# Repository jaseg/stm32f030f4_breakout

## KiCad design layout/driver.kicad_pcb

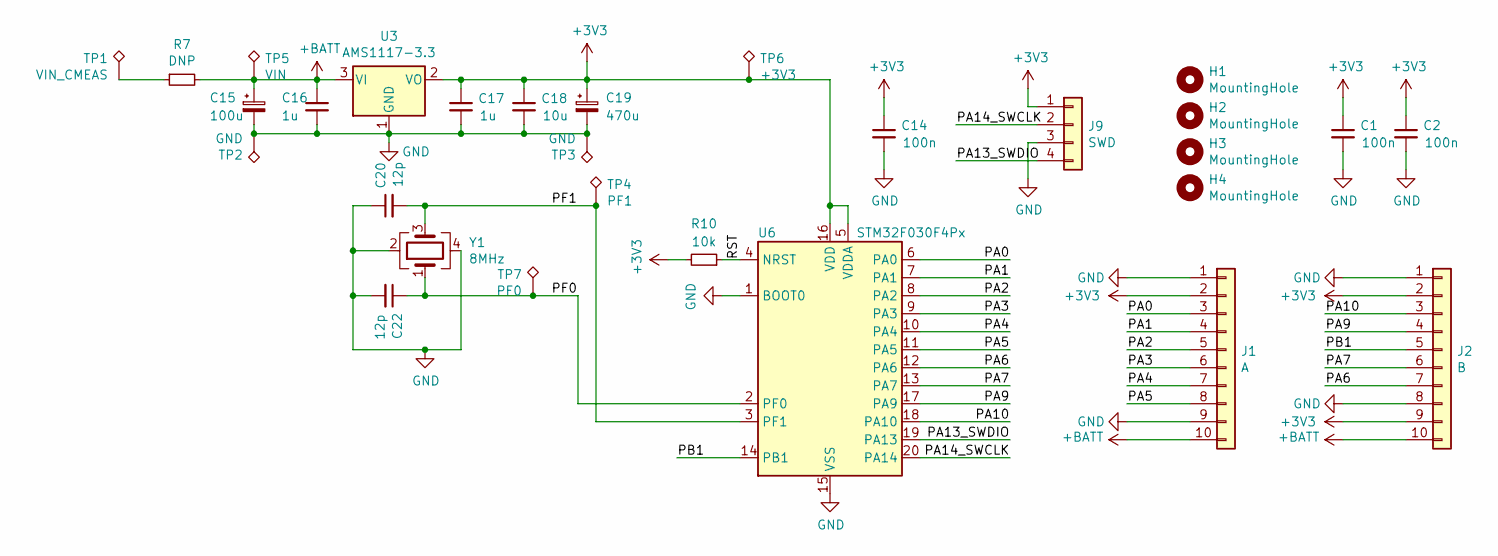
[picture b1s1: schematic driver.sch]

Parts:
C1, C2, C14: 100n; C_0603_1608Metric_Pad1.05x0.95mm_HandSolder
C15: 100u; CP_Radial_D6.3mm_P2.50mm
C16, C17: 1u; C_0603_1608Metric_Pad1.05x0.95mm_HandSolder
C18: 10u; C_0603_1608Metric_Pad1.05x0.95mm_HandSolder
C19: 470u; CP_Radial_D6.3mm_P2.50mm
C20, C22: 12p; C_0603_1608Metric_Pad1.05x0.95mm_HandSolder
H1, H2, H3, H4: MountingHole; MountingHole_3.2mm_M3
J1: A; PinHeader_1x10_P2.54mm_Vertical
J2: B; PinHeader_1x10_P2.54mm_Vertical
J9: SWD; PinHeader_1x04_P2.54mm_Vertical
R7: DNP; R_0603_1608Metric_Pad1.05x0.95mm_HandSolder
R10: 10k; R_0603_1608Metric_Pad1.05x0.95mm_HandSolder
TP1: VIN_CMEAS; TestPoint_Pad_D1.5mm
TP2: GND; TestPoint_Pad_D2.5mm
TP3: GND; TestPoint_Pad_D1.5mm
TP4: PF1; TestPoint_Pad_D1.5mm
TP5: VIN; TestPoint_Pad_D2.5mm
TP6: +3V3; TestPoint_Pad_D1.5mm
TP7: PF0; TestPoint_Pad_D1.5mm
U3: AMS1117-3.3; SOT-223-3_TabPin2
U6: STM32F030F4Px; TSSOP-20_4.4x6.5mm_P0.65mm
Y1: 8MHz; Crystal_SMD_3225-4Pin_3.2x2.5mm_HandSoldering

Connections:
+3V3: C1.1, C2.1, C14.1, C17.1, C18.1, C19.1, J1.2, J2.2, J2.9, J9.1, R10.2, TP6.1, U3.2 (VO), U6.5 (VDDA), U6.16 (VDD); also elsewhere on the board
+BATT: C15.1, C16.1, J1.10, J2.10, R7.2, TP5.1, U3.3 (VI); also elsewhere on the board
/PA0: J1.3, U6.6 (PA0)
/PA1: J1.4, U6.7 (PA1)
/PA2: J1.5, U6.8 (PA2)
/PA3: J1.6, U6.9 (PA3)
/PA4: J1.7, U6.10 (PA4)
/PA5: J1.8, U6.11 (PA5)
/PA6: J2.7, U6.12 (PA6); also elsewhere on the board
/PA7: J2.6, U6.13 (PA7); also elsewhere on the board
/PA9: J2.4, U6.17 (PA9); also elsewhere on the board
/PA10: J2.3, U6.18 (PA10); also elsewhere on the board
/PA13_SWDIO: J9.4, U6.19 (PA13)
/PA14_SWCLK: J9.2, U6.20 (PA14)
/PB1: J2.5, U6.14 (PB1); also elsewhere on the board
/PF0: C22.1, TP7.1, U6.2 (PF0), Y1.1
/PF1: C20.2, TP4.1, U6.3 (PF1), Y1.3
/RST: R10.1, U6.4 (NRST)
GND: C1.2, C2.2, C14.2, C15.2, C16.2, C17.2, C18.2, C19.2, C20.1, C22.2, J1.1, J1.9, J2.1, J2.8, J9.3, TP2.1, TP3.1, U3.1 (GND), U6.1 (BOOT0), U6.15 (VSS), Y1.2, Y1.4; also elsewhere on the board
unnamed: R7.1, TP1.1

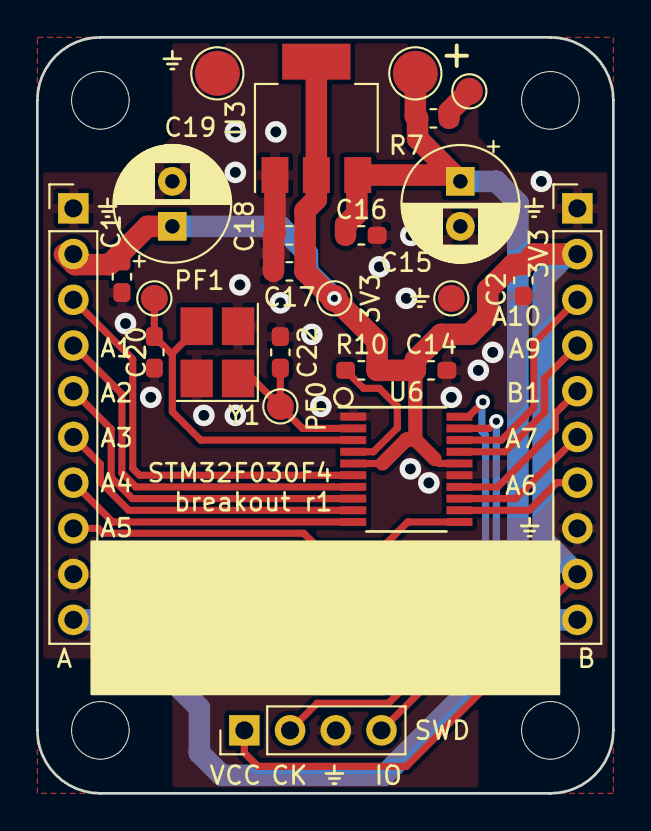
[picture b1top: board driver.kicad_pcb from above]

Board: 2 copper layers, 32.0 x 42.0 mm, 29 parts (0 on the bottom side), 20 nets.

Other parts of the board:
Jr: B; PinHeader_1x10_P2.54mm_Vertical

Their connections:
+3V3: Jr.2, Jr.9; also elsewhere on the board
+BATT: Jr.10; also elsewhere on the board
/PA6: Jr.7; also elsewhere on the board
/PA7: Jr.6; also elsewhere on the board
/PA9: Jr.4; also elsewhere on the board
/PA10: Jr.3; also elsewhere on the board
/PB1: Jr.5; also elsewhere on the board
GND: Jr.1, Jr.8; also elsewhere on the board
